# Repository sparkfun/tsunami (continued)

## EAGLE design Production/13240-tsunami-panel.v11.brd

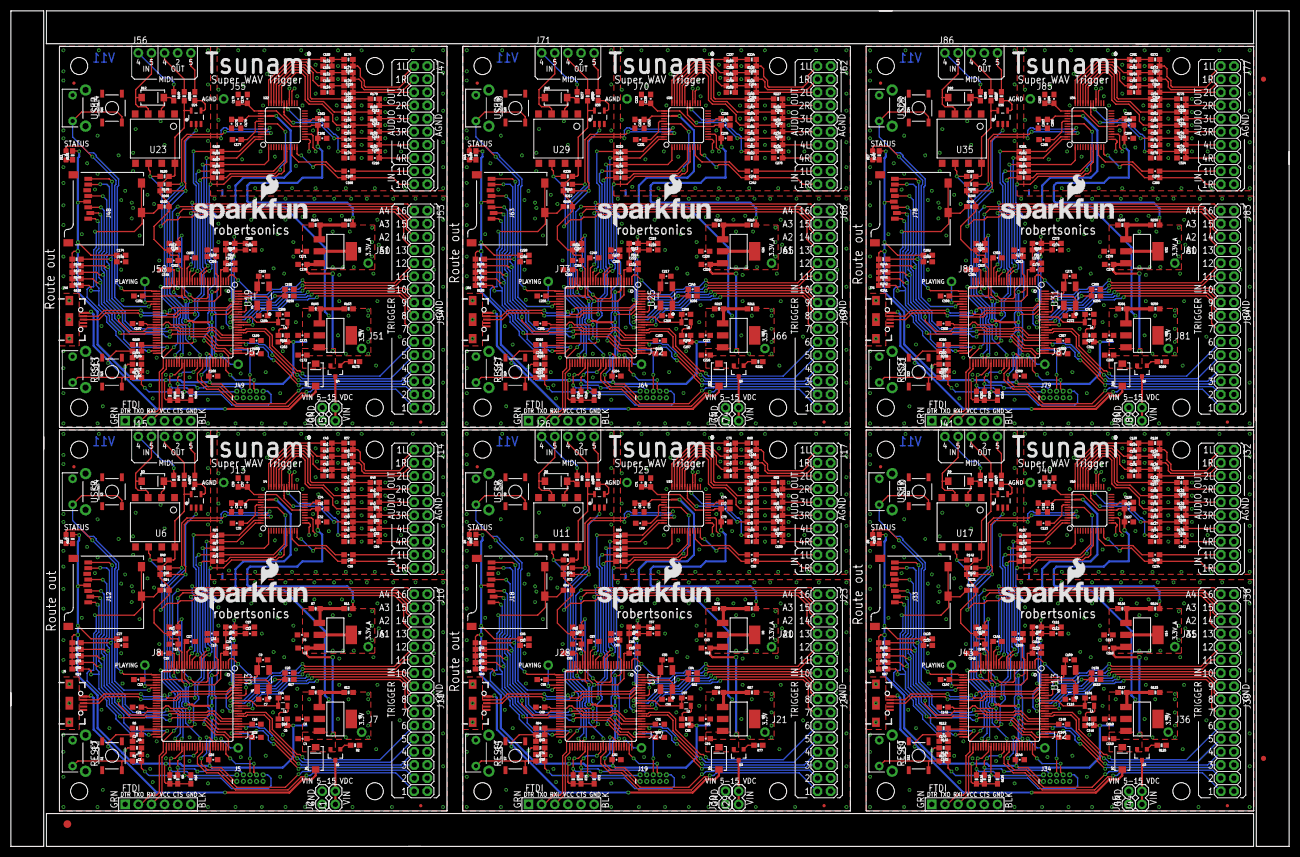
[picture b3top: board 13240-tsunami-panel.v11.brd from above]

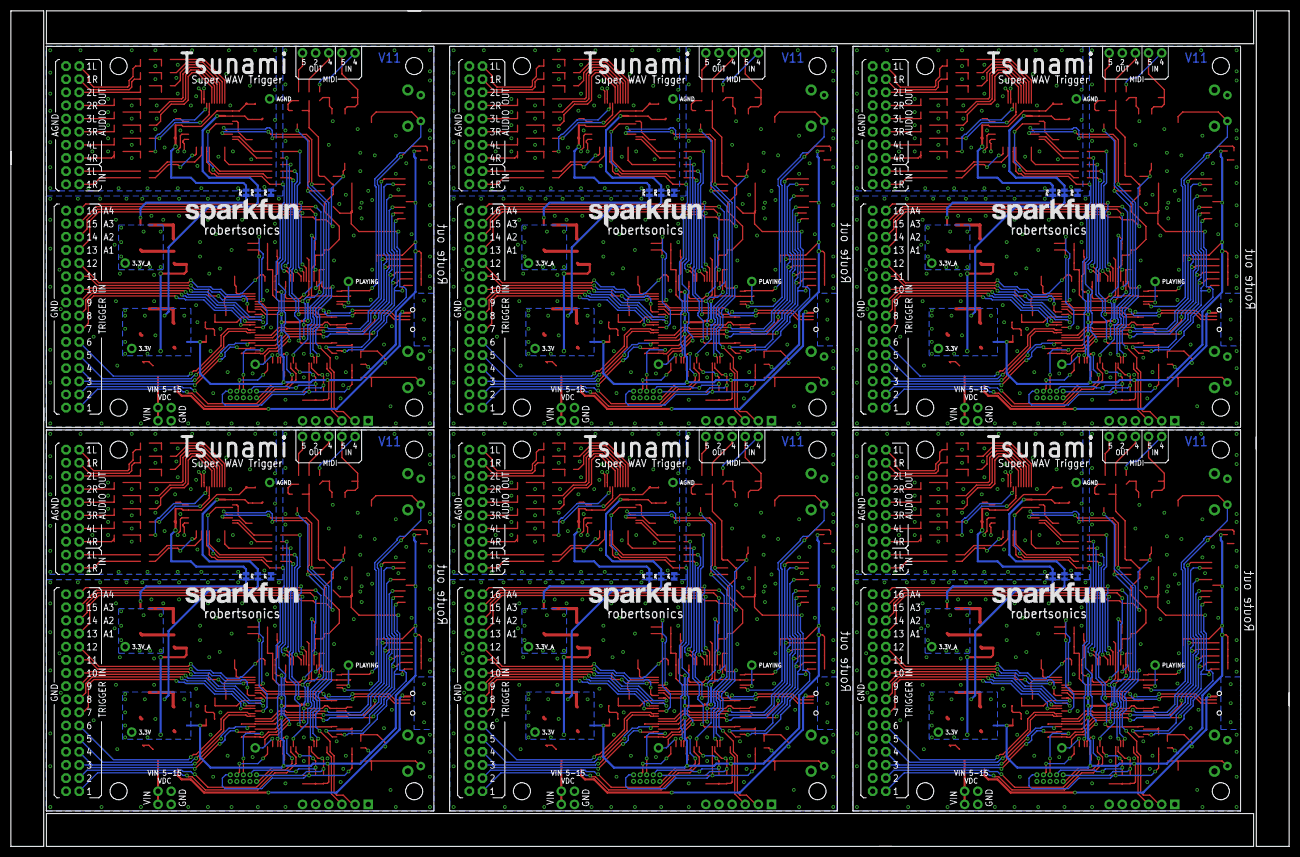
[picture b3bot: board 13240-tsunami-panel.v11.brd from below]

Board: 2 copper layers, 247.1 x 161.5 mm, 939 parts (24 on the bottom side), 678 nets.

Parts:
C1, C98, C152, C206, C260, C314: 10nF; 0603-CAP
C2, C5, C6, C11, C27, C61, C63, C65, C66, C86, C115, C117, C119, C120, C140, C169, C171, C173, C174, C194, C223, C225, C227, C228, C248, C277, C279, C281, C282, C302: 10uF; 0603-CAP
C3, C4, C8, C10, C12, C13, C15, C16, C17, C18, C19, C21, C22, C23, C24, C26, C28, C31, C35, C37, C47, C48, C49, C50, C51, C52, C53, C54, C57, C58, C59, C62, C64, C68, C70, C72, C83, C85, C87, C88, C89, C90, C91, C92, C93, C94, C95, C96, C101, C102, C103, C104, C105, C106, C107, C108, C111, C112, C113, C116, C118, C122, C124, C126, C137, C139, C141, C142, C143, C144, C145, C146, C147, C148, C149, C150, C155, C156, C157, C158, C159, C160, C161, C162, C165, C166, C167, C170, C172, C176, C178, C180, C191, C193, C195, C196, C197, C198, C199, C200, C201, C202, C203, C204, C209, C210, C211, C212, C213, C214, C215, C216, C219, C220, C221, C224, C226, C230, C232, C234, C245, C247, C249, C250, C251, C252, C253, C254, C255, C256, C257, C258, C263, C264, C265, C266, C267, C268, C269, C270, C273, C274, C275, C278, C280, C284, C286, C288, C299, C301, C303, C304, C305, C306, C307, C308, C309, C310, C311, C312, C317, C318, C319, C320, C321, C322, C323, C324: 0.1uF; 0603-CAP
C7, C9, C55, C56, C109, C110, C163, C164, C217, C218, C271, C272: 12pF; 0603-CAP
C14, C97, C151, C205, C259, C313: 4.7uF; 0603-CAP
C20, C84, C138, C192, C246, C300: 10pF; 0603-CAP
C25, C60, C114, C168, C222, C276: 2.2uF; 0603-CAP
C29, C30, C32, C33, C34, C36, C38, C39, C40, C41, C42, C43, C44, C45, C46, C67, C69, C71, C73, C74, C75, C76, C77, C78, C79, C80, C81, C82, C99, C100, C121, C123, C125, C127, C128, C129, C130, C131, C132, C133, C134, C135, C136, C153, C154, C175, C177, C179, C181, C182, C183, C184, C185, C186, C187, C188, C189, C190, C207, C208, C229, C231, C233, C235, C236, C237, C238, C239, C240, C241, C242, C243, C244, C261, C262, C283, C285, C287, C289, C290, C291, C292, C293, C294, C295, C296, C297, C298, C315, C316: 1.0uF; 0603-CAP
D1, D3, D4, D6, D7, D9, D10, D12, D13, D15, D16, D18: MBRA140; SMA-DIODE
D2, D5, D8, D11, D14, D17: BLUE; LED-0603
E$1: FIDUCIAL-1.5X3
E$7, E$8: FIDUCIAL-1X2
FB1, FB2, FB3, FB4, FB5, FB6, FB7, FB8, FB9, FB10, FB11, FB12, FB13, FB14, FB15, FB16, FB17, FB18: 470; 0603
FD1, FD2, FD3, FD4, FD5, FD6, FD7, FD8, FD9, FD10, FD11, FD12: FIDUCIALUFIDUCIAL; MICRO-FIDUCIAL
H1, H2, H3, H4, H5, H6, H7, H8, H9, H10, H11, H12, H13, H14, H15, H16, H17, H18, H19, H20, H21, H22, H23, H24: STAND-OFF
J1, J29, J44, J59, J74, J89: VDC-IN; 1X02
J2, J30, J45, J60, J75, J90: GND-IN; 1X02
J3, J27, J42, J57, J72, J87: DEBUG; 1X01_NO_SILK
J4, J16, J31, J46, J61, J76: USB-MICROB"; USB-B-MICRO-SMD_V03
J5, J19, J34, J49, J64, J79: CORTEX_DEBUGPTH; 2X5-PTH-1.27MM
J6, J20, J35, J50, J65, J80: 3.3VA; 1X01_NO_SILK
J7, J21, J36, J51, J66, J81: 3.3V; 1X01_NO_SILK
J8, J28, J43, J58, J73, J88: PLAYING; 1X01_NO_SILK
J9, J22, J37, J52, J67, J82: FTDI_DEVICE; FTDI_DEVICE_SIDE
J10, J23, J38, J53, J68, J83: TRIG2; 2X8
J11, J24, J39, J54, J69, J84: TRIG1; 2X8
J12, J18, J33, J48, J63, J78: USD-SDIO-SOCKET; MICRO-SD-SOCKET-SDIO
J13, J25, J40, J55, J70, J85: GND; 1X01_NO_SILK
J14, J17, J32, J47, J62, J77: AUDIO I/O; 2X10
J15, J26, J41, J56, J71, J86: MIDI; 1X05_NO_SILK
JP1, JP2, JP3, JP4, JP5, JP6, JP7, JP8, JP9, JP10, JP11, JP12, JP13, JP14, JP15, JP16, JP17, JP18: JUMPER-PAD-2-NC_BY_TRACENO_SILK; PAD-JUMPER-2-NC_BY_TRACE_NO_SILK
L1, L2, L3, L4, L5, L6: 10uH; 0805
LOGO1, LOGO2, LOGO5, LOGO7, LOGO9, LOGO11: SFE_LOGO_NAME.2_INCH; SFE_LOGO_NAME_.2
LOGO3, LOGO4, LOGO6, LOGO8, LOGO10, LOGO12: SFE_LOGO_NAME_FLAME.2_INCH; SFE_LOGO_NAME_FLAME_.2
Q1, Q2, Q3, Q4, Q5, Q6: 2.5A/30V; SOT23-3
R1, R75, R123, R171, R219, R267: 33; 0603-RES
R2, R77, R125, R173, R221, R269: 1M; 0603-RES
R3, R18, R23, R53, R54, R76, R101, R102, R124, R149, R150, R172, R197, R198, R220, R245, R246, R268: 10K; 0603-RES
R4, R63, R111, R159, R207, R255: 15K; 0603-RES
R5, R64, R112, R160, R208, R256: 22K; 0603-RES
R6, R9, R10, R19, R20, R21, R22, R29, R30, R31, R32, R33, R34, R35, R36, R49, R50, R51, R52, R56, R57, R58, R59, R60, R61, R70, R71, R72, R78, R79, R97, R98, R99, R100, R104, R105, R106, R107, R108, R109, R118, R119, R120, R126, R127, R145, R146, R147, R148, R152, R153, R154, R155, R156, R157, R166, R167, R168, R174, R175, R193, R194, R195, R196, R200, R201, R202, R203, R204, R205, R214, R215, R216, R222, R223, R241, R242, R243, R244, R248, R249, R250, R251, R252, R253, R262, R263, R264, R270, R271: 100k; 0603-RES
R7, R8, R68, R69, R116, R117, R164, R165, R212, R213, R260, R261: 390; 0603-RES
R11, R12, R66, R67, R114, R115, R162, R163, R210, R211, R258, R259: 240; 0603-RES
R13, R55, R103, R151, R199, R247: 330; 0603-RES
R14, R15, R73, R74, R121, R122, R169, R170, R217, R218, R265, R266: 4.7K; 0603-RES
R16, R65, R113, R161, R209, R257: 2.2; 0603-RES
R17, R62, R110, R158, R206, R254: 5.62k; 0603-RES
R24, R25, R26, R27, R28, R88, R89, R90, R91, R92, R136, R137, R138, R139, R140, R184, R185, R186, R187, R188, R232, R233, R234, R235, R236, R280, R281, R282, R283, R284: 100; 0603-RES
R37, R38, R39, R40, R41, R42, R43, R44, R80, R81, R82, R83, R84, R85, R86, R87, R128, R129, R130, R131, R132, R133, R134, R135, R176, R177, R178, R179, R180, R181, R182, R183, R224, R225, R226, R227, R228, R229, R230, R231, R272, R273, R274, R275, R276, R277, R278, R279: 10; 0603-RES
R45, R46, R47, R48, R93, R94, R95, R96, R141, R142, R143, R144, R189, R190, R191, R192, R237, R238, R239, R240, R285, R286, R287, R288: 220; 0603-RES
S1, S7, S11, S15, S19, S23: Reset; TACTILE-SWITCH-SMD
S2, S4, S5, S6, S9, S10, S13, S14, S17, S18, S21, S22: DNS; TACTILE-PTH-SIDEEZ
S3, S8, S12, S16, S20, S24: User; TACTILE-SWITCH-SMD
TP1, TP12, TP21, TP30, TP39, TP48: AIN2L; TP_15TH
TP2, TP13, TP22, TP31, TP40, TP49: AIN2R; TP_15TH
TP3, TP10, TP19, TP28, TP37, TP46: AOUT5L; TP_15TH
TP4, TP11, TP20, TP29, TP38, TP47: AOUT5R; TP_15TH
TP5, TP14, TP23, TP32, TP41, TP50: SWDIO/TMS; TP_15TH
TP6, TP15, TP24, TP33, TP42, TP51: SWCK/TCK; TP_15TH
TP7, TP16, TP25, TP34, TP43, TP52: TDO; TP_15TH
TP8, TP17, TP26, TP35, TP44, TP53: TDI; TP_15TH
TP9, TP18, TP27, TP36, TP45, TP54: NRESET; TP_15TH
U1, U2, U8, U9, U14, U15, U20, U21, U26, U27, U32, U33: LM1117; SOT223
U3, U7, U13, U19, U25, U31: ATSAMS70N20A-AN; LQFP100
U4, U10, U16, U22, U28, U34: AK4618VQ; LQFP-48
U5, U12, U18, U24, U30, U36: 74AHC1G125; SOT23-5
U6, U11, U17, U23, U29, U35: 6N138M; 8-SMD
Y1, Y2, Y3, Y4, Y5, Y6: 11.2896 MHz; CRYSTAL-OSC-SMD-5X3

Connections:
1: D6.C, R93.2, U11.2
2: D9.C, R141.2, U17.2
3: D12.C, R189.2, U23.2
3.3V: C6.1, C8.1, C10.1, C11.1, C12.1, C13.1, C15.1, C16.1, C27.1, C28.1, C35.1, C36.1, FB3.1, J5.1, J7.1, J12.VCC, JP2.1, JP2.2, R3.2, R6.2, R9.2, R10.2, R12.2, R13.2, R14.2, R15.2, R16.1, R18.2, R19.2, R20.2, R21.2, R22.2, R23.2, R47.2, R48.2, U2.2, U2.4, U3.5, U3.19, U3.28, U3.68, U3.81, U3.93, U4.39, U5.5, U6.8
3.3V1: C61.1, C65.1, C66.1, C67.1, C70.1, C83.1, C91.1, C92.1, C93.1, C94.1, C95.1, C96.1, FB6.1, J18.VCC, J19.1, J21.1, JP6.1, JP6.2, R49.2, R50.2, R51.2, R52.2, R53.2, R54.2, R55.2, R65.1, R67.2, R70.2, R71.2, R72.2, R73.2, R74.2, R76.2, R94.2, R95.2, U7.5, U7.19, U7.28, U7.68, U7.81, U7.93, U9.2, U9.4, U10.39, U11.8, U12.5
3.3V2: C115.1, C119.1, C120.1, C121.1, C124.1, C137.1, C145.1, C146.1, C147.1, C148.1, C149.1, C150.1, FB9.1, J33.VCC, J34.1, J36.1, JP9.1, JP9.2, R97.2, R98.2, R99.2, R100.2, R101.2, R102.2, R103.2, R113.1, R115.2, R118.2, R119.2, R120.2, R121.2, R122.2, R124.2, R142.2, R143.2, U13.5, U13.19, U13.28, U13.68, U13.81, U13.93, U15.2, U15.4, U16.39, U17.8, U18.5
3.3V3: C169.1, C173.1, C174.1, C175.1, C178.1, C191.1, C199.1, C200.1, C201.1, C202.1, C203.1, C204.1, FB12.1, J48.VCC, J49.1, J51.1, JP12.1, JP12.2, R145.2, R146.2, R147.2, R148.2, R149.2, R150.2, R151.2, R161.1, R163.2, R166.2, R167.2, R168.2, R169.2, R170.2, R172.2, R190.2, R191.2, U19.5, U19.19, U19.28, U19.68, U19.81, U19.93, U21.2, U21.4, U22.39, U23.8, U24.5
3.3V4: C223.1, C227.1, C228.1, C229.1, C232.1, C245.1, C253.1, C254.1, C255.1, C256.1, C257.1, C258.1, FB15.1, J63.VCC, J64.1, J66.1, JP15.1, JP15.2, R193.2, R194.2, R195.2, R196.2, R197.2, R198.2, R199.2, R209.1, R211.2, R214.2, R215.2, R216.2, R217.2, R218.2, R220.2, R238.2, R239.2, U25.5, U25.19, U25.28, U25.68, U25.81, U25.93, U27.2, U27.4, U28.39, U29.8, U30.5
3.3V5: C277.1, C281.1, C282.1, C283.1, C286.1, C299.1, C307.1, C308.1, C309.1, C310.1, C311.1, C312.1, FB18.1, J78.VCC, J79.1, J81.1, JP18.1, JP18.2, R241.2, R242.2, R243.2, R244.2, R245.2, R246.2, R247.2, R257.1, R259.2, R262.2, R263.2, R264.2, R265.2, R266.2, R268.2, R286.2, R287.2, U31.5, U31.19, U31.28, U31.68, U31.81, U31.93, U33.2, U33.4, U34.39, U35.8, U36.5
4: D15.C, R237.2, U29.2
5: D18.C, R285.2, U35.2
56: D3.C, R45.2, U6.2
AIN1L: C29.1, J14.17
AIN1L1: C79.1, J17.17
AIN1L2: C133.1, J32.17
AIN1L3: C187.1, J47.17
AIN1L4: C241.1, J62.17
AIN1L5: C295.1, J77.17
AIN1R: C30.1, J14.19
AIN1R1: C80.1, J17.19
AIN1R2: C134.1, J32.19
AIN1R3: C188.1, J47.19
AIN1R4: C242.1, J62.19
AIN1R5: C296.1, J77.19
AIN2L: TP1.P$1, U4.13
AIN2L1: TP12.P$1, U10.13
AIN2L2: TP21.P$1, U16.13
AIN2L3: TP30.P$1, U22.13
AIN2L4: TP39.P$1, U28.13
AIN2L5: TP48.P$1, U34.13
AIN2R: TP2.P$1, U4.15
AIN2R1: TP13.P$1, U10.15
AIN2R2: TP22.P$1, U16.15
AIN2R3: TP31.P$1, U22.15
AIN2R4: TP40.P$1, U28.15
AIN2R5: TP49.P$1, U34.15
AOUT1L: C47.1, J14.1, R37.2
AOUT1L1: C101.1, J17.1, R80.2
AOUT1L2: C155.1, J32.1, R128.2
AOUT1L3: C209.1, J47.1, R176.2
AOUT1L4: C263.1, J62.1, R224.2
AOUT1L5: C317.1, J77.1, R272.2
AOUT1R: C48.1, J14.3, R38.2
AOUT1R1: C102.1, J17.3, R81.2
AOUT1R2: C156.1, J32.3, R129.2
AOUT1R3: C210.1, J47.3, R177.2
AOUT1R4: C264.1, J62.3, R225.2
AOUT1R5: C318.1, J77.3, R273.2
AOUT2L: C49.1, J14.5, R39.2
AOUT2L1: C103.1, J17.5, R82.2
AOUT2L2: C157.1, J32.5, R130.2
AOUT2L3: C211.1, J47.5, R178.2
AOUT2L4: C265.1, J62.5, R226.2
AOUT2L5: C319.1, J77.5, R274.2
AOUT2R: C50.1, J14.7, R40.2
AOUT2R1: C104.1, J17.7, R83.2
AOUT2R2: C158.1, J32.7, R131.2
AOUT2R3: C212.1, J47.7, R179.2
AOUT2R4: C266.1, J62.7, R227.2
AOUT2R5: C320.1, J77.7, R275.2
AOUT3L: C51.1, J14.9, R41.2
AOUT3L1: C105.1, J17.9, R84.2
AOUT3L2: C159.1, J32.9, R132.2
AOUT3L3: C213.1, J47.9, R180.2
AOUT3L4: C267.1, J62.9, R228.2
AOUT3L5: C321.1, J77.9, R276.2
AOUT3R: C52.1, J14.11, R42.2
AOUT3R1: C106.1, J17.11, R85.2
AOUT3R2: C160.1, J32.11, R133.2
AOUT3R3: C214.1, J47.11, R181.2
AOUT3R4: C268.1, J62.11, R229.2
AOUT3R5: C322.1, J77.11, R277.2
AOUT4L: C53.1, J14.13, R43.2
AOUT4L1: C107.1, J17.13, R86.2
AOUT4L2: C161.1, J32.13, R134.2
AOUT4L3: C215.1, J47.13, R182.2
AOUT4L4: C269.1, J62.13, R230.2
AOUT4L5: C323.1, J77.13, R278.2
AOUT4R: C54.1, J14.15, R44.2
AOUT4R1: C108.1, J17.15, R87.2
AOUT4R2: C162.1, J32.15, R135.2
AOUT4R3: C216.1, J47.15, R183.2
AOUT4R4: C270.1, J62.15, R231.2
AOUT4R5: C324.1, J77.15, R279.2
APDN: U3.70, U4.8
APDN1: U7.70, U10.8
APDN2: U13.70, U16.8
APDN3: U19.70, U22.8
APDN4: U25.70, U28.8
APDN5: U31.70, U34.8
BCLK: R26.1, U3.11
BCLK1: R90.1, U7.11
BCLK2: R138.1, U13.11
BCLK3: R186.1, U19.11
BCLK4: R234.1, U25.11
BCLK5: R282.1, U31.11
BCLK_C: R26.2, U4.48
BCLK_C1: R90.2, U10.48
BCLK_C2: R138.2, U16.48
BCLK_C3: R186.2, U22.48
BCLK_C4: R234.2, U28.48
BCLK_C5: R282.2, U34.48
DBUG: J3.1, U3.72
DBUG1: J27.1, U7.72
DBUG2: J42.1, U13.72
DBUG3: J57.1, U19.72
DBUG4: J72.1, U25.72
DBUG5: J87.1, U31.72
GND: C1.2, C2.2, C3.2, C4.2, C5.2, C6.2, C7.2, C8.2, C9.2, C10.2, C11.2, C12.2, C13.2, C14.2, C15.2, C16.2, C17.2, C18.2, C19.2, C20.2, C21.2, C22.2, C23.2, C24.2, C25.2, C26.2, C27.2, C28.2, C31.2, C32.2, C33.2, C34.2, C35.2, C36.2, C37.2, C38.2, C47.2, C48.2, C49.2, C50.2, C51.2, C52.2, C53.2, C54.2, J2.1, J2.2, J4.GND, J5.3, J5.5, J5.9, J9.P$6, J10.2, J10.4, J10.6, J10.8, J10.10, J10.12, J10.14, J10.16, J11.2, J11.4, J11.6, J11.8, J11.10, J11.12, J11.14, J11.16, J12.GND, J12.GND1, J12.GND3, J13.1, J14.2, J14.4, J14.6, J14.8, J14.10, J14.12, J14.14, J14.16, J14.18, J14.20, J15.4, JP3.1, JP3.2, R2.1, R5.1, R7.1, R8.1, R17.1, R29.1, R30.1, R31.1, R32.1, R33.1, R34.1, R35.1, R36.1, S1.1, S2.1, S3.1, S4.1, U3.3, U3.6, U3.7, U3.8, U3.10, U3.29, U3.67, U4.2, U4.3, U4.4, U4.5, U4.6, U4.19, U4.38, U4.40, U5.1, U5.3, U6.5, Y1.2, Y1.4
GND1: C55.2, C56.2, C57.2, C58.2, C59.2, C60.2, C61.2, C62.2, C63.2, C64.2, C65.2, C66.2, C67.2, C68.2, C69.2, C70.2, C71.2, C72.2, C73.2, C74.2, C83.2, C84.2, C85.2, C86.2, C87.2, C88.2, C89.2, C90.2, C91.2, C92.2, C93.2, C94.2, C95.2, C96.2, C97.2, C98.2, C101.2, C102.2, C103.2, C104.2, C105.2, C106.2, C107.2, C108.2, J16.GND, J17.2, J17.4, J17.6, J17.8, J17.10, J17.12, J17.14, J17.16, J17.18, J17.20, J18.GND, J18.GND1, J18.GND3, J19.3, J19.5, J19.9, J22.P$6, J23.2, J23.4, J23.6, J23.8, J23.10, J23.12, J23.14, J23.16, J24.2, J24.4, J24.6, J24.8, J24.10, J24.12, J24.14, J24.16, J25.1, J26.4, J30.1, J30.2, JP4.1, JP4.2, R56.1, R57.1, R58.1, R59.1, R60.1, R61.1, R62.1, R64.1, R68.1, R69.1, R77.1, R78.1, R79.1, S5.1, S6.1, S7.1, S8.1, U7.3, U7.6, U7.7, U7.8, U7.10, U7.29, U7.67, U10.2, U10.3, U10.4, U10.5, U10.6, U10.19, U10.38, U10.40, U11.5, U12.1, U12.3, Y2.2, Y2.4
GND2: C109.2, C110.2, C111.2, C112.2, C113.2, C114.2, C115.2, C116.2, C117.2, C118.2, C119.2, C120.2, C121.2, C122.2, C123.2, C124.2, C125.2, C126.2, C127.2, C128.2, C137.2, C138.2, C139.2, C140.2, C141.2, C142.2, C143.2, C144.2, C145.2, C146.2, C147.2, C148.2, C149.2, C150.2, C151.2, C152.2, C155.2, C156.2, C157.2, C158.2, C159.2, C160.2, C161.2, C162.2, J31.GND, J32.2, J32.4, J32.6, J32.8, J32.10, J32.12, J32.14, J32.16, J32.18, J32.20, J33.GND, J33.GND1, J33.GND3, J34.3, J34.5, J34.9, J37.P$6, J38.2, J38.4, J38.6, J38.8, J38.10, J38.12, J38.14, J38.16, J39.2, J39.4, J39.6, J39.8, J39.10, J39.12, J39.14, J39.16, J40.1, J41.4, J45.1, J45.2, JP7.1, JP7.2, R104.1, R105.1, R106.1, R107.1, R108.1, R109.1, R110.1, R112.1, R116.1, R117.1, R125.1, R126.1, R127.1, S9.1, S10.1, S11.1, S12.1, U13.3, U13.6, U13.7, U13.8, U13.10, U13.29, U13.67, U16.2, U16.3, U16.4, U16.5, U16.6, U16.19, U16.38, U16.40, U17.5, U18.1, U18.3, Y3.2, Y3.4
GND3: C163.2, C164.2, C165.2, C166.2, C167.2, C168.2, C169.2, C170.2, C171.2, C172.2, C173.2, C174.2, C175.2, C176.2, C177.2, C178.2, C179.2, C180.2, C181.2, C182.2, C191.2, C192.2, C193.2, C194.2, C195.2, C196.2, C197.2, C198.2, C199.2, C200.2, C201.2, C202.2, C203.2, C204.2, C205.2, C206.2, C209.2, C210.2, C211.2, C212.2, C213.2, C214.2, C215.2, C216.2, J46.GND, J47.2, J47.4, J47.6, J47.8, J47.10, J47.12, J47.14, J47.16, J47.18, J47.20, J48.GND, J48.GND1, J48.GND3, J49.3, J49.5, J49.9, J52.P$6, J53.2, J53.4, J53.6, J53.8, J53.10, J53.12, J53.14, J53.16, J54.2, J54.4, J54.6, J54.8, J54.10, J54.12, J54.14, J54.16, J55.1, J56.4, J60.1, J60.2, JP10.1, JP10.2, R152.1, R153.1, R154.1, R155.1, R156.1, R157.1, R158.1, R160.1, R164.1, R165.1, R173.1, R174.1, R175.1, S13.1, S14.1, S15.1, S16.1, U19.3, U19.6, U19.7, U19.8, U19.10, U19.29, U19.67, U22.2, U22.3, U22.4, U22.5, U22.6, U22.19, U22.38, U22.40, U23.5, U24.1, U24.3, Y4.2, Y4.4
GND4: C217.2, C218.2, C219.2, C220.2, C221.2, C222.2, C223.2, C224.2, C225.2, C226.2, C227.2, C228.2, C229.2, C230.2, C231.2, C232.2, C233.2, C234.2, C235.2, C236.2, C245.2, C246.2, C247.2, C248.2, C249.2, C250.2, C251.2, C252.2, C253.2, C254.2, C255.2, C256.2, C257.2, C258.2, C259.2, C260.2, C263.2, C264.2, C265.2, C266.2, C267.2, C268.2, C269.2, C270.2, J61.GND, J62.2, J62.4, J62.6, J62.8, J62.10, J62.12, J62.14, J62.16, J62.18, J62.20, J63.GND, J63.GND1, J63.GND3, J64.3, J64.5, J64.9, J67.P$6, J68.2, J68.4, J68.6, J68.8, J68.10, J68.12, J68.14, J68.16, J69.2, J69.4, J69.6, J69.8, J69.10, J69.12, J69.14, J69.16, J70.1, J71.4, J75.1, J75.2, JP13.1, JP13.2, R200.1, R201.1, R202.1, R203.1, R204.1, R205.1, R206.1, R208.1, R212.1, R213.1, R221.1, R222.1, R223.1, S17.1, S18.1, S19.1, S20.1, U25.3, U25.6, U25.7, U25.8, U25.10, U25.29, U25.67, U28.2, U28.3, U28.4, U28.5, U28.6, U28.19, U28.38, U28.40, U29.5, U30.1, U30.3, Y5.2, Y5.4
GND5: C271.2, C272.2, C273.2, C274.2, C275.2, C276.2, C277.2, C278.2, C279.2, C280.2, C281.2, C282.2, C283.2, C284.2, C285.2, C286.2, C287.2, C288.2, C289.2, C290.2, C299.2, C300.2, C301.2, C302.2, C303.2, C304.2, C305.2, C306.2, C307.2, C308.2, C309.2, C310.2, C311.2, C312.2, C313.2, C314.2, C317.2, C318.2, C319.2, C320.2, C321.2, C322.2, C323.2, C324.2, J76.GND, J77.2, J77.4, J77.6, J77.8, J77.10, J77.12, J77.14, J77.16, J77.18, J77.20, J78.GND, J78.GND1, J78.GND3, J79.3, J79.5, J79.9, J82.P$6, J83.2, J83.4, J83.6, J83.8, J83.10, J83.12, J83.14, J83.16, J84.2, J84.4, J84.6, J84.8, J84.10, J84.12, J84.14, J84.16, J85.1, J86.4, J90.1, J90.2, JP16.1, JP16.2, R248.1, R249.1, R250.1, R251.1, R252.1, R253.1, R254.1, R256.1, R260.1, R261.1, R269.1, R270.1, R271.1, S21.1, S22.1, S23.1, S24.1, U31.3, U31.6, U31.7, U31.8, U31.10, U31.29, U31.67, U34.2, U34.3, U34.4, U34.5, U34.6, U34.19, U34.38, U34.40, U35.5, U36.1, U36.3, Y6.2, Y6.4
HSDM: J4.D-, U3.94
HSDM1: J16.D-, U7.94
HSDM2: J31.D-, U13.94
HSDM3: J46.D-, U19.94
HSDM4: J61.D-, U25.94
HSDM5: J76.D-, U31.94
HSDP: J4.D+, U3.95
HSDP1: J16.D+, U7.95
HSDP2: J31.D+, U13.95
HSDP3: J46.D+, U19.95
HSDP4: J61.D+, U25.95
HSDP5: J76.D+, U31.95
I2C_SCK: R15.1, U3.55, U4.46
I2C_SCK1: R74.1, U7.55, U10.46
I2C_SCK2: R122.1, U13.55, U16.46
I2C_SCK3: R170.1, U19.55, U22.46
I2C_SCK4: R218.1, U25.55, U28.46
I2C_SCK5: R266.1, U31.55, U34.46
I2C_SDA: R14.1, U3.64, U4.45
I2C_SDA1: R73.1, U7.64, U10.45
I2C_SDA2: R121.1, U13.64, U16.45
I2C_SDA3: R169.1, U19.64, U22.45
I2C_SDA4: R217.1, U25.64, U28.45
I2C_SDA5: R265.1, U31.64, U34.45
LRCK: R27.1, U3.12
LRCK1: R91.1, U7.12
LRCK2: R139.1, U13.12
LRCK3: R187.1, U19.12
LRCK4: R235.1, U25.12
LRCK5: R283.1, U31.12
LRCK_C: R27.2, U4.1
LRCK_C1: R91.2, U10.1
LRCK_C2: R139.2, U16.1
LRCK_C3: R187.2, U22.1
LRCK_C4: R235.2, U28.1
LRCK_C5: R283.2, U34.1
MCLK: R25.1, U3.15
MCLK1: R89.1, U7.15
MCLK2: R137.1, U13.15
MCLK3: R185.1, U19.15
MCLK4: R233.1, U25.15
MCLK5: R281.1, U31.15
MCLK_C: R25.2, U4.47
MCLK_C1: R89.2, U10.47
MCLK_C2: R137.2, U16.47
MCLK_C3: R185.2, U22.47
MCLK_C4: R233.2, U28.47
MCLK_C5: R281.2, U34.47
MIDI-IN-PIN1: J26.1, R93.1
MIDI-IN-PIN2: D6.A, J26.2, U11.3
MIDI-IN-PIN3: J41.1, R141.1
MIDI-IN-PIN4: J15.1, R45.1
MIDI-IN-PIN5: D3.A, J15.2, U6.3
MIDI-IN-PIN6: D9.A, J41.2, U17.3
MIDI-IN-PIN7: J56.1, R189.1
MIDI-IN-PIN8: D12.A, J56.2, U23.3
MIDI-IN-PIN9: J71.1, R237.1
MIDI-IN-PIN10: D15.A, J71.2, U29.3
MIDI-IN-PIN11: J86.1, R285.1
MIDI-IN-PIN12: D18.A, J86.2, U35.3
MIDI-OUT-PIN1: J26.3, R95.1
MIDI-OUT-PIN2: J26.5, R96.2
MIDI-OUT-PIN3: J41.3, R143.1
MIDI-OUT-PIN4: J15.3, R47.1
MIDI-OUT-PIN5: J15.5, R46.2
MIDI-OUT-PIN6: J41.5, R144.2
MIDI-OUT-PIN7: J56.3, R191.1
MIDI-OUT-PIN8: J56.5, R192.2
MIDI-OUT-PIN9: J71.3, R239.1
MIDI-OUT-PIN10: J71.5, R240.2
MIDI-OUT-PIN11: J86.3, R287.1
MIDI-OUT-PIN12: J86.5, R288.2
MIN: R48.1, U3.75, U6.6
MIN1: R94.1, U7.75, U11.6
MIN2: R142.1, U13.75, U17.6
MIN3: R190.1, U19.75, U23.6
MIN4: R238.1, U25.75, U29.6
MIN5: R286.1, U31.75, U35.6
MOUT: U3.56, U5.2
MOUT1: U7.56, U12.2
MOUT2: U13.56, U18.2
MOUT3: U19.56, U24.2
MOUT4: U25.56, U30.2
MOUT5: U31.56, U36.2
unnamed: C7.1, U3.98, Y1.1
unnamed: C9.1, U3.99, Y1.3
unnamed: C19.1, FB1.1, U3.96
unnamed: C14.1, L1.2, U3.90
unnamed: C23.1, FB2.1, U3.86
unnamed: C33.1, U4.41
unnamed: C56.1, U7.98, Y2.1
unnamed: J8.1, U3.30
unnamed: C55.1, U7.99, Y2.3
unnamed: D2.C, U3.31
unnamed: D2.A, R13.1
unnamed: C34.1, U4.20
unnamed: C40.1, U4.36
unnamed: C30.2, U4.12
unnamed: C29.2, U4.10
unnamed: C20.1, R17.2, U3.97
unnamed: C26.1, FB3.2, U3.9
unnamed: C43.1, U4.35
unnamed: C45.1, U4.34
unnamed: C41.1, U4.33
unnamed: C44.1, U4.32
unnamed: C46.1, U4.31
unnamed: C40.2, R31.2, R37.1
unnamed: L1.1, R16.2
unnamed: R7.2, R11.1, U1.1
unnamed: R1.1, S1.3, S2.2
unnamed: C42.2, R30.2, R44.1
unnamed: C39.2, R29.2, R43.1
unnamed: R8.2, R12.1, U2.1
unnamed: C46.2, R36.2, R42.1
unnamed: C39.1, U4.30
unnamed: C42.1, U4.29
unnamed: TP3.P$1, U4.28
unnamed: TP4.P$1, U4.27
unnamed: C57.1, FB4.1, U7.96
unnamed: C58.1, FB5.1, U7.86
unnamed: D5.C, U7.31
unnamed: R46.1, U5.4
unnamed: C69.1, U10.41
unnamed: C74.1, U10.20
unnamed: C80.2, U10.12
unnamed: C79.2, U10.10
unnamed: C75.1, U10.36
unnamed: C76.1, U10.35
unnamed: C77.1, U10.34
unnamed: C78.1, U10.33
unnamed: C81.1, U10.32
unnamed: C82.1, U10.31
unnamed: C84.1, R62.2, U7.97
unnamed: C85.1, FB6.2, U7.9
unnamed: D5.A, R55.1
unnamed: C44.2, R35.2, R41.1
unnamed: C41.2, R34.2, R40.1
unnamed: C43.2, R32.2, R38.1
unnamed: C45.2, R33.2, R39.1
unnamed: C97.1, L2.2, U7.90
unnamed: L2.1, R65.2
unnamed: R66.1, R68.2, U8.1
unnamed: R67.1, R69.2, U9.1
unnamed: R75.1, S5.2, S7.3
unnamed: C99.1, U10.30
unnamed: C100.1, U10.29
unnamed: TP10.P$1, U10.28
unnamed: TP11.P$1, U10.27
unnamed: Q2.1, R77.2
unnamed: C75.2, R56.2, R80.1
unnamed: C100.2, R78.2, R87.1
unnamed: C99.2, R79.2, R86.1
unnamed: C82.2, R61.2, R85.1
unnamed: C81.2, R60.2, R84.1
unnamed: C78.2, R59.2, R83.1
unnamed: C76.2, R57.2, R81.1
unnamed: C77.2, R58.2, R82.1
unnamed: R96.1, U12.4
unnamed: Q1.1, R2.2
unnamed: J28.1, U7.30
unnamed: C110.1, U13.98, Y3.1
unnamed: C109.1, U13.99, Y3.3
unnamed: C111.1, FB7.1, U13.96
unnamed: C112.1, FB8.1, U13.86
unnamed: D8.C, U13.31
unnamed: C123.1, U16.41
unnamed: C128.1, U16.20
unnamed: C134.2, U16.12
unnamed: C133.2, U16.10
unnamed: C129.1, U16.36
unnamed: C130.1, U16.35
unnamed: C131.1, U16.34
unnamed: C132.1, U16.33
unnamed: C135.1, U16.32
unnamed: C136.1, U16.31
unnamed: C138.1, R110.2, U13.97
unnamed: C139.1, FB9.2, U13.9
unnamed: D8.A, R103.1
unnamed: C151.1, L3.2, U13.90
unnamed: L3.1, R113.2
unnamed: R114.1, R116.2, U14.1
unnamed: R115.1, R117.2, U15.1
unnamed: R123.1, S9.2, S11.3
unnamed: C153.1, U16.30
unnamed: C154.1, U16.29
unnamed: TP19.P$1, U16.28
unnamed: TP20.P$1, U16.27
unnamed: Q3.1, R125.2
unnamed: C129.2, R104.2, R128.1
unnamed: C154.2, R126.2, R135.1
unnamed: C153.2, R127.2, R134.1
unnamed: C136.2, R109.2, R133.1
unnamed: C135.2, R108.2, R132.1
unnamed: C132.2, R107.2, R131.1
unnamed: C130.2, R105.2, R129.1
unnamed: C131.2, R106.2, R130.1
unnamed: R144.1, U18.4
unnamed: J43.1, U13.30
unnamed: C164.1, U19.98, Y4.1
unnamed: C163.1, U19.99, Y4.3
unnamed: C165.1, FB10.1, U19.96
unnamed: C166.1, FB11.1, U19.86
unnamed: D11.C, U19.31
unnamed: C177.1, U22.41
unnamed: C182.1, U22.20
unnamed: C188.2, U22.12
unnamed: C187.2, U22.10
unnamed: C183.1, U22.36
unnamed: C184.1, U22.35
unnamed: C185.1, U22.34
unnamed: C186.1, U22.33
unnamed: C189.1, U22.32
unnamed: C190.1, U22.31
unnamed: C192.1, R158.2, U19.97
unnamed: C193.1, FB12.2, U19.9
unnamed: D11.A, R151.1
unnamed: C205.1, L4.2, U19.90
unnamed: L4.1, R161.2
unnamed: R162.1, R164.2, U20.1
unnamed: R163.1, R165.2, U21.1
unnamed: R171.1, S13.2, S15.3
unnamed: C207.1, U22.30
unnamed: C208.1, U22.29
unnamed: TP28.P$1, U22.28
unnamed: TP29.P$1, U22.27
unnamed: Q4.1, R173.2
unnamed: C183.2, R152.2, R176.1
unnamed: C208.2, R174.2, R183.1
unnamed: C207.2, R175.2, R182.1
unnamed: C190.2, R157.2, R181.1
unnamed: C189.2, R156.2, R180.1
unnamed: C186.2, R155.2, R179.1
unnamed: C184.2, R153.2, R177.1
unnamed: C185.2, R154.2, R178.1
unnamed: R192.1, U24.4
unnamed: J58.1, U19.30
unnamed: C218.1, U25.98, Y5.1
unnamed: C217.1, U25.99, Y5.3
unnamed: C219.1, FB13.1, U25.96
unnamed: C220.1, FB14.1, U25.86
unnamed: D14.C, U25.31
unnamed: C231.1, U28.41
unnamed: C236.1, U28.20
unnamed: C242.2, U28.12
unnamed: C241.2, U28.10
unnamed: C237.1, U28.36
unnamed: C238.1, U28.35
unnamed: C239.1, U28.34
unnamed: C240.1, U28.33
unnamed: C243.1, U28.32
unnamed: C244.1, U28.31
unnamed: C246.1, R206.2, U25.97
unnamed: C247.1, FB15.2, U25.9
unnamed: D14.A, R199.1
unnamed: C259.1, L5.2, U25.90
unnamed: L5.1, R209.2
unnamed: R210.1, R212.2, U26.1
unnamed: R211.1, R213.2, U27.1
unnamed: R219.1, S17.2, S19.3
unnamed: C261.1, U28.30
unnamed: C262.1, U28.29
unnamed: TP37.P$1, U28.28
unnamed: TP38.P$1, U28.27
unnamed: Q5.1, R221.2
unnamed: C237.2, R200.2, R224.1
unnamed: C262.2, R222.2, R231.1
unnamed: C261.2, R223.2, R230.1
unnamed: C244.2, R205.2, R229.1
unnamed: C243.2, R204.2, R228.1
unnamed: C240.2, R203.2, R227.1
unnamed: C238.2, R201.2, R225.1
unnamed: C239.2, R202.2, R226.1
unnamed: R240.1, U30.4
unnamed: J73.1, U25.30
unnamed: C272.1, U31.98, Y6.1
unnamed: C271.1, U31.99, Y6.3
unnamed: C273.1, FB16.1, U31.96
unnamed: C274.1, FB17.1, U31.86
unnamed: D17.C, U31.31
unnamed: C285.1, U34.41
unnamed: C290.1, U34.20
unnamed: C296.2, U34.12
unnamed: C295.2, U34.10
unnamed: C291.1, U34.36
unnamed: C292.1, U34.35
unnamed: C293.1, U34.34
unnamed: C294.1, U34.33
unnamed: C297.1, U34.32
unnamed: C298.1, U34.31
unnamed: C300.1, R254.2, U31.97
unnamed: C301.1, FB18.2, U31.9
unnamed: D17.A, R247.1
unnamed: C313.1, L6.2, U31.90
unnamed: L6.1, R257.2
unnamed: R258.1, R260.2, U32.1
unnamed: R259.1, R261.2, U33.1
unnamed: R267.1, S21.2, S23.3
unnamed: C315.1, U34.30
unnamed: C316.1, U34.29
unnamed: TP46.P$1, U34.28
unnamed: TP47.P$1, U34.27
unnamed: Q6.1, R269.2
unnamed: C291.2, R248.2, R272.1
unnamed: C316.2, R270.2, R279.1
unnamed: C315.2, R271.2, R278.1
unnamed: C298.2, R253.2, R277.1
unnamed: C297.2, R252.2, R276.1
unnamed: C294.2, R251.2, R275.1
unnamed: C292.2, R249.2, R273.1
unnamed: C293.2, R250.2, R274.1
unnamed: R288.1, U36.4
unnamed: J88.1, U31.30
NRESET: C1.1, J5.10, R1.2, R3.1, R10.1, TP9.P$1, U3.58
NRESET1: C98.1, J19.10, R72.1, R75.2, R76.1, TP18.P$1, U7.58
NRESET2: C152.1, J34.10, R120.1, R123.2, R124.1, TP27.P$1, U13.58
NRESET3: C206.1, J49.10, R168.1, R171.2, R172.1, TP36.P$1, U19.58
NRESET4: C260.1, J64.10, R216.1, R219.2, R220.1, TP45.P$1, U25.58
NRESET5: C314.1, J79.10, R264.1, R267.2, R268.1, TP54.P$1, U31.58
REGINPUTS: C3.1, C4.1, D1.C, Q1.2, U1.3, U2.3
REGINPUTS1: C62.1, C64.1, D4.C, Q2.2, U8.3, U9.3
REGINPUTS2: C116.1, C118.1, D7.C, Q3.2, U14.3, U15.3
REGINPUTS3: C170.1, C172.1, D10.C, Q4.2, U20.3, U21.3
REGINPUTS4: C224.1, C226.1, D13.C, Q5.2, U26.3, U27.3
REGINPUTS5: C278.1, C280.1, D16.C, Q6.2, U32.3, U33.3
RXD: J9.P$3, U3.51
RXD1: J22.P$3, U7.51
RXD2: J37.P$3, U13.51
RXD3: J52.P$3, U19.51
RXD4: J67.P$3, U25.51
RXD5: J82.P$3, U31.51
SDCD: J12.CD1, J12.CD2, R18.1, U3.49
SDCD1: J18.CD1, J18.CD2, R54.1, U7.49
SDCD2: J33.CD1, J33.CD2, R102.1, U13.49
SDCD3: J48.CD1, J48.CD2, R150.1, U19.49
SDCD4: J63.CD1, J63.CD2, R198.1, U25.49
SDCD5: J78.CD1, J78.CD2, R246.1, U31.49
SDCLK: J12.CLK, U3.40
SDCLK1: J18.CLK, U7.40
SDCLK2: J33.CLK, U13.40
SDCLK3: J48.CLK, U19.40
SDCLK4: J63.CLK, U25.40
SDCLK5: J78.CLK, U31.40
SDCMD: J12.CMD, R23.1, U3.79
SDCMD1: J18.CMD, R53.1, U7.79
SDCMD2: J33.CMD, R101.1, U13.79
SDCMD3: J48.CMD, R149.1, U19.79
SDCMD4: J63.CMD, R197.1, U25.79
SDCMD5: J78.CMD, R245.1, U31.79
SDD0: J12.DAT0, R21.1, U3.82
SDD1: J12.DAT1, R22.1, U3.83
SDD2: J12.DAT2, R19.1, U3.42
SDD3: J12.CD/DAT3, R20.1, U3.50
SDD4: J18.DAT0, R51.1, U7.82
SDD5: J18.DAT1, R52.1, U7.83
SDD6: J18.DAT2, R49.1, U7.42
SDD7: J18.CD/DAT3, R50.1, U7.50
SDD8: J33.DAT0, R99.1, U13.82
SDD9: J33.DAT1, R100.1, U13.83
SDD10: J33.DAT2, R97.1, U13.42
SDD11: J33.CD/DAT3, R98.1, U13.50
SDD12: J48.DAT0, R147.1, U19.82
SDD13: J48.DAT1, R148.1, U19.83
SDD14: J48.DAT2, R145.1, U19.42
SDD15: J48.CD/DAT3, R146.1, U19.50
SDD16: J63.DAT0, R195.1, U25.82
SDD17: J63.DAT1, R196.1, U25.83
SDD18: J63.DAT2, R193.1, U25.42
SDD19: J63.CD/DAT3, R194.1, U25.50
SDD20: J78.DAT0, R243.1, U31.82
SDD21: J78.DAT1, R244.1, U31.83
SDD22: J78.DAT2, R241.1, U31.42
SDD23: J78.CD/DAT3, R242.1, U31.50
SHIELD: J4.SHIELD1, J4.SHIELD2, J4.SHIELD3
SHIELD1: J16.SHIELD1, J16.SHIELD2, J16.SHIELD3
SHIELD2: J31.SHIELD1, J31.SHIELD2, J31.SHIELD3
SHIELD3: J46.SHIELD1, J46.SHIELD2, J46.SHIELD3
SHIELD4: J61.SHIELD1, J61.SHIELD2, J61.SHIELD3
SHIELD5: J76.SHIELD1, J76.SHIELD2, J76.SHIELD3
SWCLK/TCK: J5.4, R9.1, TP6.P$1, U3.63
SWCLK/TCK1: J19.4, R71.1, TP15.P$1, U7.63
SWCLK/TCK2: J34.4, R119.1, TP24.P$1, U13.63
SWCLK/TCK3: J49.4, R167.1, TP33.P$1, U19.63
SWCLK/TCK4: J64.4, R215.1, TP42.P$1, U25.63
SWCLK/TCK5: J79.4, R263.1, TP51.P$1, U31.63
SWDIO/TMS: J5.2, R6.1, TP5.P$1, U3.57
SWDIO/TMS1: J19.2, R70.1, TP14.P$1, U7.57
SWDIO/TMS2: J34.2, R118.1, TP23.P$1, U13.57
SWDIO/TMS3: J49.2, R166.1, TP32.P$1, U19.57
SWDIO/TMS4: J64.2, R214.1, TP41.P$1, U25.57
SWDIO/TMS5: J79.2, R262.1, TP50.P$1, U31.57
TDI: J5.8, TP8.P$1, U3.74
TDI1: J19.8, TP17.P$1, U7.74
TDI2: J34.8, TP26.P$1, U13.74
TDI3: J49.8, TP35.P$1, U19.74
TDI4: J64.8, TP44.P$1, U25.74
TDI5: J79.8, TP53.P$1, U31.74
TDMI: R24.1, U3.46
TDMI1: R88.1, U7.46
TDMI2: R136.1, U13.46
TDMI3: R184.1, U19.46
TDMI4: R232.1, U25.46
TDMI5: R280.1, U31.46
TDMI_C: R24.2, U4.42
TDMI_C1: R88.2, U10.42
TDMI_C2: R136.2, U16.42
TDMI_C3: R184.2, U22.42
TDMI_C4: R232.2, U28.42
TDMI_C5: R280.2, U34.42
TDMO: R28.1, U3.36
TDMO1: R92.1, U7.36
TDMO2: R140.1, U13.36
TDMO3: R188.1, U19.36
TDMO4: R236.1, U25.36
TDMO5: R284.1, U31.36
TDMO_C: R28.2, U4.7
TDMO_C1: R92.2, U10.7
TDMO_C2: R140.2, U16.7
TDMO_C3: R188.2, U22.7
TDMO_C4: R236.2, U28.7
TDMO_C5: R284.2, U34.7
TDO: J5.6, TP7.P$1, U3.77
TDO1: J19.6, TP16.P$1, U7.77
TDO2: J34.6, TP25.P$1, U13.77
TDO3: J49.6, TP34.P$1, U19.77
TDO4: J64.6, TP43.P$1, U25.77
TDO5: J79.6, TP52.P$1, U31.77
TXD: J9.P$2, U3.23
TXD1: J22.P$2, U7.23
TXD2: J37.P$2, U13.23
TXD3: J52.P$2, U19.23
TXD4: J67.P$2, U25.23
TXD5: J82.P$2, U31.23
UIA1: J10.7, U3.17
UIA2: J10.5, U3.20
UIA3: J10.3, U3.21
UIA4: J10.1, U3.16
UIA5: J23.7, U7.17
UIA6: J23.5, U7.20
UIA7: J23.3, U7.21
UIA8: J23.1, U7.16
UIA9: J38.7, U13.17
UIA10: J38.5, U13.20
UIA11: J38.3, U13.21
UIA12: J38.1, U13.16
UIA13: J53.7, U19.17
UIA14: J53.5, U19.20
UIA15: J53.3, U19.21
UIA16: J53.1, U19.16
UIA17: J68.7, U25.17
UIA18: J68.5, U25.20
UIA19: J68.3, U25.21
UIA20: J68.1, U25.16
UIA21: J83.7, U31.17
UIA22: J83.5, U31.20
UIA23: J83.3, U31.21
UIA24: J83.1, U31.16
UID1: J11.15, U3.65
UID2: J11.13, U3.69
UID3: J11.11, U3.78
UID4: J11.9, U3.80
UID5: J11.7, U3.84
UID6: J11.5, U3.85
UID7: J11.3, U3.87
UID8: J11.1, U3.88
UID9: J10.15, U3.89
UID10: J10.13, U3.91
UID11: J10.11, U3.92
UID12: J10.9, U3.1
UID13: J24.15, U7.65
UID14: J24.13, U7.69
UID15: J24.11, U7.78
UID16: J24.9, U7.80
UID17: J24.7, U7.84
UID18: J24.5, U7.85
UID19: J24.3, U7.87
UID20: J24.1, U7.88
UID21: J23.15, U7.89
UID22: J23.11, U7.92
UID23: J23.9, U7.1
UID24: J23.13, U7.91
UID25: J39.15, U13.65
UID26: J39.13, U13.69
UID27: J39.11, U13.78
UID28: J39.9, U13.80
UID29: J39.7, U13.84
UID30: J39.5, U13.85
UID31: J39.3, U13.87
UID32: J39.1, U13.88
UID33: J38.15, U13.89
UID34: J38.11, U13.92
UID35: J38.9, U13.1
UID36: J38.13, U13.91
UID37: J54.15, U19.65
UID38: J54.13, U19.69
UID39: J54.11, U19.78
UID40: J54.9, U19.80
UID41: J54.7, U19.84
UID42: J54.5, U19.85
UID43: J54.3, U19.87
UID44: J54.1, U19.88
UID45: J53.15, U19.89
UID46: J53.11, U19.92
UID47: J53.9, U19.1
UID48: J53.13, U19.91
UID49: J69.15, U25.65
UID50: J69.13, U25.69
UID51: J69.11, U25.78
UID52: J69.9, U25.80
UID53: J69.7, U25.84
UID54: J69.5, U25.85
UID55: J69.3, U25.87
UID56: J69.1, U25.88
UID57: J68.15, U25.89
UID58: J68.11, U25.92
UID59: J68.9, U25.1
UID60: J68.13, U25.91
UID61: J84.15, U31.65
UID62: J84.13, U31.69
UID63: J84.11, U31.78
UID64: J84.9, U31.80
UID65: J84.7, U31.84
UID66: J84.5, U31.85
UID67: J84.3, U31.87
UID68: J84.1, U31.88
UID69: J83.15, U31.89
UID70: J83.11, U31.92
UID71: J83.9, U31.1
UID72: J83.13, U31.91
USERSW: S3.3, S4.2, U3.26
USERSW1: S6.2, S8.3, U7.26
USERSW2: S10.2, S12.3, U13.26
USERSW3: S14.2, S16.3, U19.26
USERSW4: S18.2, S20.3, U25.26
USERSW5: S22.2, S24.3, U31.26
VBDET: R4.1, R5.2, U3.47
VBDET1: R63.1, R64.2, U7.47
VBDET2: R111.1, R112.2, U13.47
VBDET3: R159.1, R160.2, U19.47
VBDET4: R207.1, R208.2, U25.47
VBDET5: R255.1, R256.2, U31.47
VBUS: C2.1, D1.A, J4.VBUS, R4.2
VBUS1: C86.1, D4.A, J16.VBUS, R63.2
VBUS2: C140.1, D7.A, J31.VBUS, R111.2
VBUS3: C194.1, D10.A, J46.VBUS, R159.2
VBUS4: C248.1, D13.A, J61.VBUS, R207.2
VBUS5: C302.1, D16.A, J76.VBUS, R255.2
VCCA: C5.1, C31.1, C32.1, C37.1, C38.1, J6.1, JP1.1, JP1.2, R11.2, U1.2, U1.4, U4.18, U4.37
VCCA1: C63.1, C68.1, C71.1, C72.1, C73.1, J20.1, JP5.1, JP5.2, R66.2, U8.2, U8.4, U10.18, U10.37
VCCA2: C117.1, C122.1, C125.1, C126.1, C127.1, J35.1, JP8.1, JP8.2, R114.2, U14.2, U14.4, U16.18, U16.37
VCCA3: C171.1, C176.1, C179.1, C180.1, C181.1, J50.1, JP11.1, JP11.2, R162.2, U20.2, U20.4, U22.18, U22.37
VCCA4: C225.1, C230.1, C233.1, C234.1, C235.1, J65.1, JP14.1, JP14.2, R210.2, U26.2, U26.4, U28.18, U28.37
VCCA5: C279.1, C284.1, C287.1, C288.1, C289.1, J80.1, JP17.1, JP17.2, R258.2, U32.2, U32.4, U34.18, U34.37
VDDOUT: C17.1, C18.1, C21.1, C22.1, C24.1, C25.1, FB1.2, FB2.2, U3.4, U3.18, U3.22, U3.39, U3.76
VDDOUT1: C59.1, C60.1, C87.1, C88.1, C89.1, C90.1, FB4.2, FB5.2, U7.4, U7.18, U7.22, U7.39, U7.76
VDDOUT2: C113.1, C114.1, C141.1, C142.1, C143.1, C144.1, FB7.2, FB8.2, U13.4, U13.18, U13.22, U13.39, U13.76
VDDOUT3: C167.1, C168.1, C195.1, C196.1, C197.1, C198.1, FB10.2, FB11.2, U19.4, U19.18, U19.22, U19.39, U19.76
VDDOUT4: C221.1, C222.1, C249.1, C250.1, C251.1, C252.1, FB13.2, FB14.2, U25.4, U25.18, U25.22, U25.39, U25.76
VDDOUT5: C275.1, C276.1, C303.1, C304.1, C305.1, C306.1, FB16.2, FB17.2, U31.4, U31.18, U31.22, U31.39, U31.76
VIN: J1.1, J1.2, Q1.3
VIN1: J29.1, J29.2, Q2.3
VIN2: J44.1, J44.2, Q3.3
VIN3: J59.1, J59.2, Q4.3
VIN4: J74.1, J74.2, Q5.3
VIN5: J89.1, J89.2, Q6.3

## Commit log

2015-12-23 Initial commit of boilerplate repo structure.
2015-12-23 Jamie's first draft hardware files.
2015-12-23 Second update from Jamie
2015-12-23 Fixed unconnected nets and missing cap values.
2015-12-23 Changing dashed line to info layer.
    So ERC doesn't think it's a net.
2015-12-24 Replaced generic resistors and capacitors with SparkFun versions.
2015-12-24 Started a design notes document in the Doc folder.
2015-12-24 Updated Design Notes to markdown
2015-12-24 Added SAM S70 and AK4618 datasheets.
2015-12-25 Updated Design Notes doc.
2016-01-11 First pass over schematic.
    Mostly changing flag style on signals.
2016-01-11 Second pass over schematic
    -Swapped crystal for smaller one.
    -Updated SD card connector with SDIO signal names.
2016-01-11 A little more WIP
    -uSD socket had SDIO naming on pins.
    -pushed parts around PCB.
2016-01-12 Ongoing progress.
    Filled out "layout checklist" in Atmel docs.
    Pushed & pulled components to closer to final proximity.
2016-01-14 Updates all around
    Adjusted LQFP land patterns.
    Switched to LM1117 Vregs.
    Added library to gitignore.
    Ongoing ratsnest work.
2016-01-14 More updates.
    Schematic logos, partitioning & labeling.
    Found a few more absent pullup resistors.
2016-01-18 WIP.
    Checking in so I can traverse project history for a moment.
2016-01-18 Added reset switch & some labeling.
    Still WIP.
2016-01-19 Continuing work.
    Labeling, & sizing mostly complete.
    About ready to route.
2016-01-20 Ready to start routing.
    If I need to fall back, this is the one.
2016-01-21 Routing in progress.
2016-01-22 Routing nearly complete.
2016-01-23 Ready for group review.
2016-01-25 Updates after Monday morning review.
2016-01-26 Adding PROD IDs to components.
2016-01-28 Swapped location of SD socket and reset switches.
    Added some more branding to silkscreen.
2016-02-04 Revising power input.
    Using RG Keen's "ideal diode" for barrel input, avoiding a diode drop on
    the barrel input, so it's prioritized over Vusb if both are plugged in.
2016-02-05 Quick DRC fixes.
2016-02-05 Adding DNS designation to barrel jack.
2016-07-11 Tsunami - very first WIP
    As adapted from Tapestry.
2016-07-12 Work in progress...
    ...MIDI added, many other small updates.
2016-07-12 More incremental progress.
2016-07-14 More work in progress.
    In pretty good shape, but a lot of lingering fit & finish work needed.
2016-07-18 Proofreading and other touchups.
2016-07-20 Board updates - nearing completion.
2016-07-20 Waypoint before renumbering.
2016-07-20 Lots of little issues handled - did a prelim checklist.
2016-07-20 Somehow forgot schem with last commit.
2016-07-22 Re-ordering MIDI output pins...
    ...so that they match the pin ordering on a DIN-5.
2016-07-26 One more ground stitch via
2016-07-26 Moving Tapestry board files into a "deprecated" folder.
2016-08-01 Updates from reviews.
2016-08-02 Some checklist touchups
    JTAG TP's placed on 50 mil grid.
2016-08-04 Addressing Eric's punch list.
    See issue #2
2016-11-01 Updates for production.
    Silkscreen touchups.
    -all silk on back is right side up.
    -some size & placement adjustments to labels. Name is larger, some pad
    labels are smaller.
    -JTAG and DEBUG labels removed from both sides of board.
    -Playing is active high, overbar deleted.
2016-11-07 Post review & production checklist.
    -Centered staking vias on USB.
    -Moved some vias to avoid silk.
    -Text touchups around V reg outputs.
2016-11-14 Fixing Eric's checklist issues.
2016-11-15 panel
2016-11-29 Fixing mislabeled MIDI out.
    Pin labels on 2 and 5 were transposed.
2016-11-29 Fixing silkscreen labels on panel.
    Transposed 2 and 5 labels on MIDI out port.
    Rolled version to V11 on all files.
2017-02-16 Deleting unused directories.
2017-02-16 Fixing readme.
